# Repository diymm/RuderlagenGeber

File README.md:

## RuderlagenGeber NMEA 2000
Sensor im Eigenbau mit N2K Schnittstelle.

### Mechanischer Aufbau
Durch die Verwendung von Aluminium Blechteilen und Normteilen wird 
ein preisgünstigen Aufbau ermöglicht.\
Die Positionserfassung erfolgt magnetisch verschleissfrei und wird über 360°,\
ohne Anschlag erfasst. Eine mechanische Ausrichtung des Gebers ist nicht notwendig.
Über einen Taster wird die 0° Grad Position festgelegt und\
es kann eine Drehrichtungsumkehr eingeschaltet werden.

### Elektronik
Die Schaltung ist gegen Verpolung und Spannungspitzen geschützt\
und besteht im wesentlichen aus drei Komponenten:\
Dem Positionssensor AS5600\
einem CAN BUS Controller MCP2515\
und dem Kontroller SAMD21G17.\
Die Spannungsregelung wird energiesparend über einen Schaltregler geregelt. 
 
### Firmware
Die Firmware ist aktuell noch in der Testphase und wird noch ergänzt.
Im Testmode werden über die RS232 TTL verschiedene Zustände und Messwerte angezeigt,
auch ohne Ausgabe der Werte ist es mit Hilfe der LED möglich den Abstand des Magnetsensors
ausreichend genau einzustellen. 

### Vorstellung des Projekts auf YouTube
Eine Video Unterstützung auf YouTube steht zur weiteren Unterstützung bereit.

### Dokumentation
Durch die Verendung von KiCad für den Schaltplan und FreeCAD für die Zeichnungen ist eine Anpassung
an eigene Vorstellungen möglich.

### Lizenz
Alle Zeichnungen und der Programmcode können frei, nicht kommerziell, verwendet werden.\
creative commons (CC BY-NC 4.0) https://creativecommons.org/licenses/

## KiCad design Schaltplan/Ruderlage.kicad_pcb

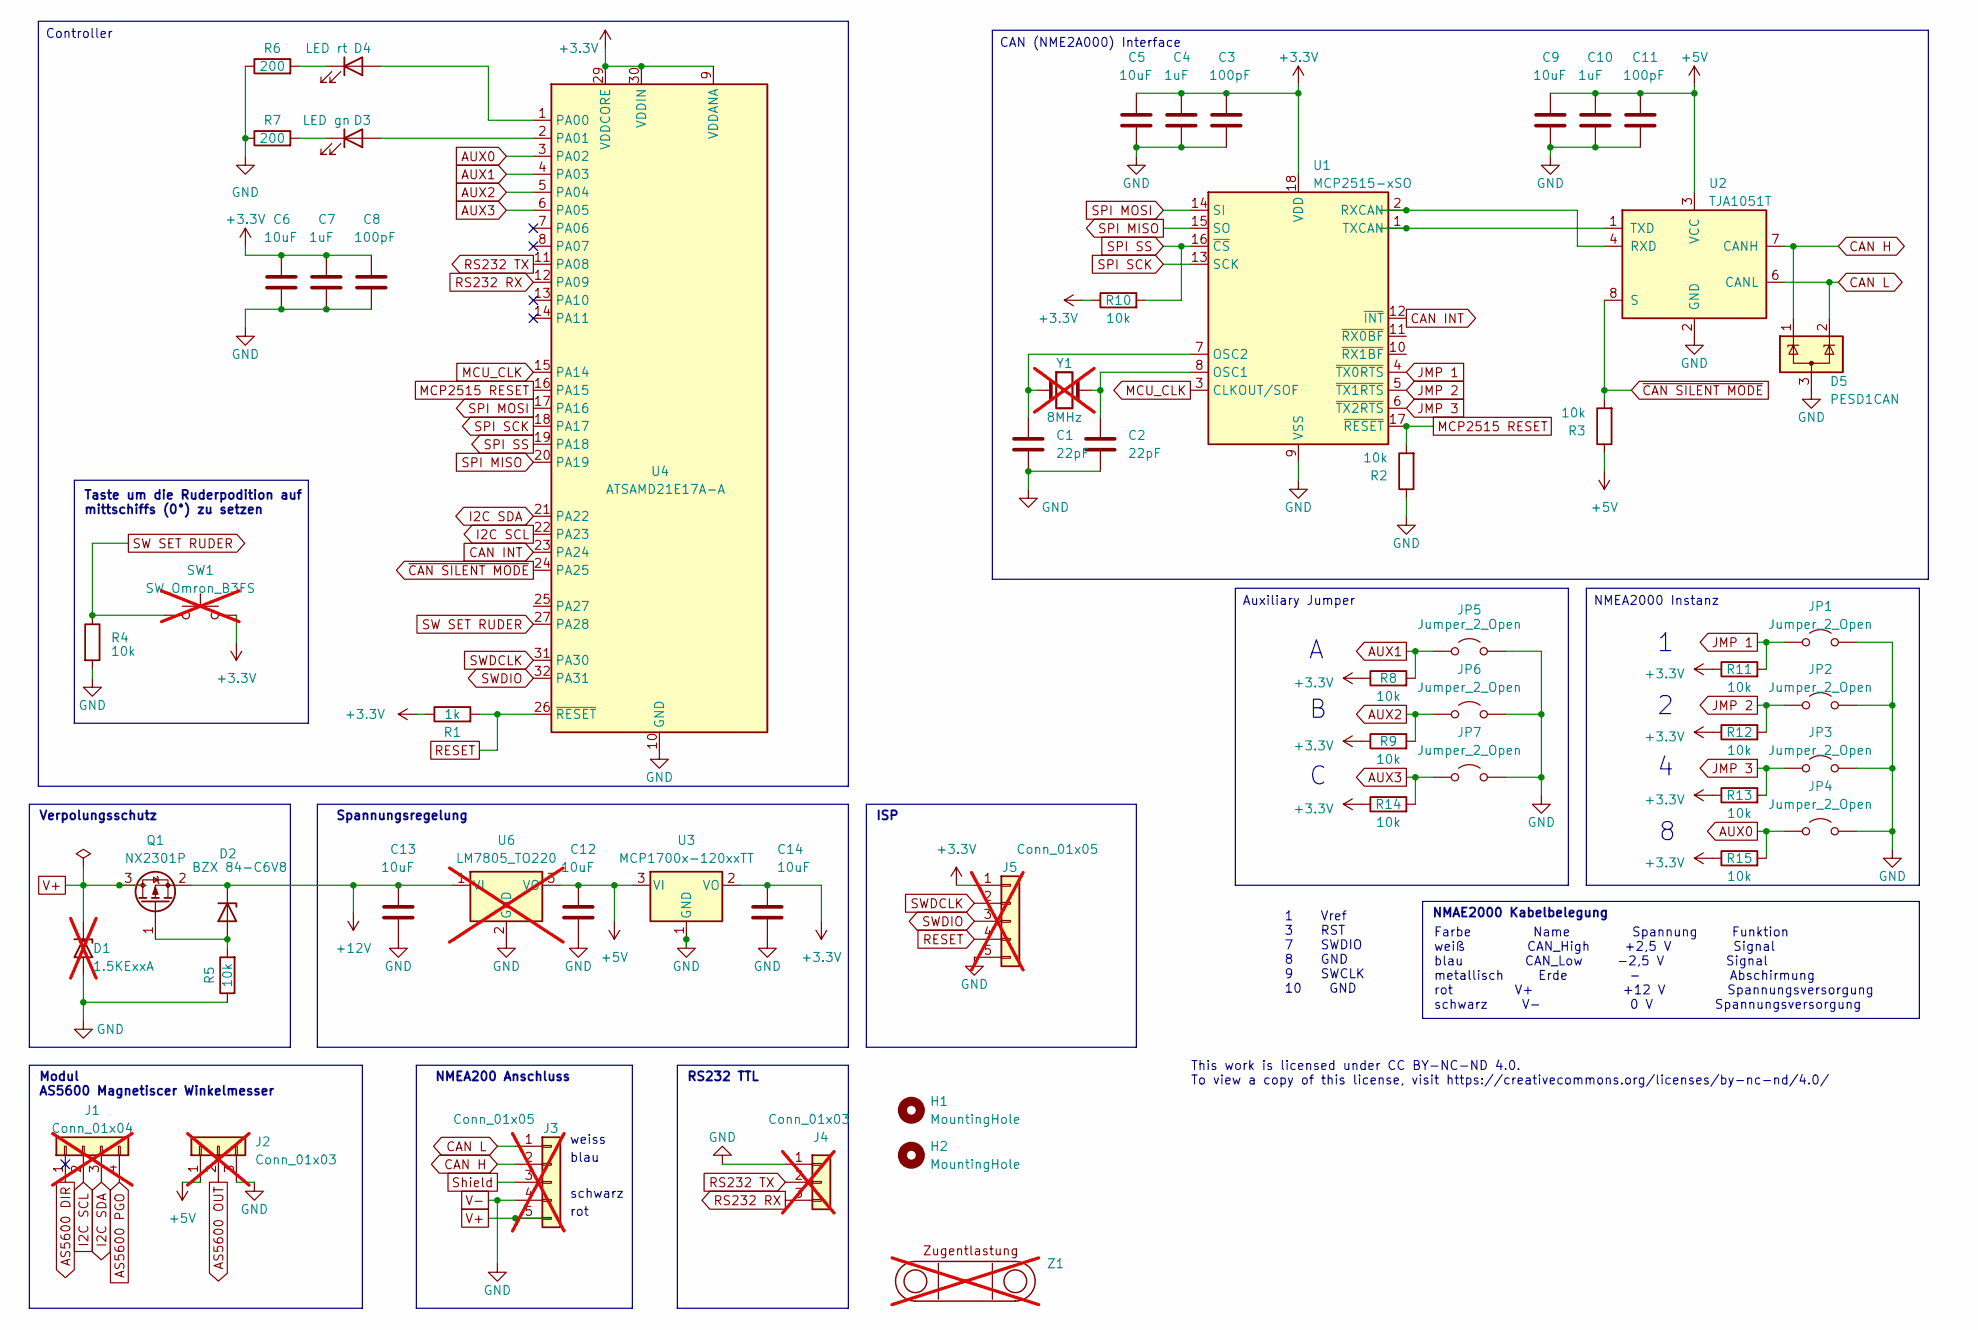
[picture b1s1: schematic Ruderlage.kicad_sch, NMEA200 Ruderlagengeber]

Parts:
C1, C2: 22pF; C_0805_2012Metric
C3, C8, C11: 100pF; C_0805_2012Metric; LCSC C9900195991
C4, C7, C10: 1uF; C_0805_2012Metric
C5, C6, C9, C12, C13, C14: 10uF; C_0805_2012Metric
D1: 1.5KExxA; D_DO-201AE_P15.24mm_Horizontal; not fitted
D2: BZX 84-C6V8; SOT-23
D3: LED gn; LED_0805_2012Metric
D4: LED rt; LED_0805_2012Metric
D5: PESD1CAN; SOT-23
H1, H2: MountingHole; MountingHole_5mm
J1: Conn_01x04; PinHeader_1x04_P2.54mm_Vertical; not fitted
J2, J4: Conn_01x03; PinHeader_1x03_P2.54mm_Vertical; not fitted
J3, J5: Conn_01x05; PinHeader_1x05_P2.54mm_Vertical; not fitted
JP1, JP2, JP3, JP4, JP5, JP6, JP7: Jumper_2_Open; SolderJumper-2_P1.3mm_Open_RoundedPad1.0x1.5mm
Q1: NX2301P; SOT-23; LCSC C551594
R1: 1k; R_0805_2012Metric; LCSC C9900143942
R2, R8, R9, R10, R11, R14, R15: 10k; R_0805_2012Metric; LCSC C9900234692
R3, R4, R5, R12, R13: 10k; R_0805_2012Metric
R6, R7: 200; R_0805_2012Metric; LCSC C2889551
SW1: SW_Omron_B3FS; SW_TH_Tactile_Omron_B3F-10xx; not fitted
U1: MCP2515-xSO; SOIC-18W_7.5x11.6mm_P1.27mm
U2: TJA1051T; SOIC-8_3.9x4.9mm_P1.27mm
U3: MCP1700x-120xxTT; SOT-23
U4: ATSAMD21E17A-A; TQFP-32_7x7mm_P0.8mm; LCSC C618766
U6: LM7805_TO220; TO-220-3_Vertical; not fitted
Y1: 8MHz; Crystal_HC49-4H_Vertical; not fitted
Z1: Zugentlastung; not fitted

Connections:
+3.3V: C3.1, C4.1, C5.1, C6.1, C7.1, C8.1, C14.1, J5.1, R1.1, R8.1, R9.1, R10.1, R11.1, R12.1, R13.1, R14.1, R15.1, SW1.2, U1.18 (VDD), U3.2 (VO), U4.9 (VDDANA), U4.29 (VDDCORE), U4.30 (VDDIN)
+5V: C9.1, C10.1, C11.1, C12.1, J2.1, R3.1, U2.3 (VCC), U3.3 (VI), U6.3 (VO)
+12V: C13.1, D2.3 (K), Q1.2 (S), U6.1 (VI)
AS5600 DIR: J1.1
AS5600 OUT: J2.2
AS5600 PGO: J1.4
AUX0: JP4.1 (A), R15.2, U4.3 (PA02)
AUX1: JP5.1 (A), R8.2, U4.4 (PA03)
AUX2: JP6.1 (A), R9.2, U4.5 (PA04)
AUX3: JP7.1 (A), R14.2, U4.6 (PA05)
CAN H: D5.1 (K), J3.2, U2.7 (CANH)
CAN INT: U1.12 (~INT), U4.23 (PA24)
CAN L: D5.2 (K), J3.1, U2.6 (CANL)
I2C SCL: J1.2, U4.22 (PA23)
I2C SDA: J1.3, U4.21 (PA22)
JMP 1: JP1.1 (A), R11.2, U1.4 (~TX0RTS)
JMP 2: JP2.1 (A), R12.2, U1.5 (~TX1RTS)
JMP 3: JP3.1 (A), R13.2, U1.6 (~TX2RTS)
MCP2515 RESET: R2.2, U1.17 (~RESET), U4.16 (PA15)
MCU_CLK: U1.3 (CLKOUT/SOF), U4.15 (PA14)
unnamed: D2.1 (A), Q1.1 (G), R5.2
unnamed: D3.2 (A), U4.2 (PA01)
unnamed: D3.1 (K), R7.2
unnamed: D4.2 (A), U4.1 (PA00)
unnamed: D4.1 (K), R6.2
unnamed: C2.1, U1.8 (OSC1), Y1.2
unnamed: C1.1, U1.7 (OSC2), Y1.1
unnamed: U1.2 (RXCAN), U2.4 (RXD)
unnamed: U1.1 (TXCAN), U2.1 (TXD)
RESET: J5.4, R1.2, U4.26 (~RESET)
RS232 RX: J4.3, U4.12 (PA09)
RS232 TX: J4.2, U4.11 (PA08)
SPI MISO: U1.15 (SO), U4.20 (PA19)
SPI MOSI: U1.14 (SI), U4.17 (PA16)
SPI SCK: U1.13 (SCK), U4.18 (PA17)
SPI SS: R10.2, U1.16 (~CS), U4.19 (PA18)
SW SET RUDER: R4.1, SW1.1, U4.27 (PA28)
SWDCLK: J5.2, U4.31 (PA30)
SWDIO: J5.3, U4.32 (PA31)
Shield: J3.3
V+: D1.1 (A1), J3.5, Q1.3 (D)
V-: C1.2, C2.2, C3.2, C4.2, C5.2, C6.2, C7.2, C8.2, C9.2, C10.2, C11.2, C12.2, C13.2, C14.2, D1.2 (A2), D5.3 (A), J2.3, J3.4, J4.1, J5.5, JP1.2 (B), JP2.2 (B), JP3.2 (B), JP4.2 (B), JP5.2 (B), JP6.2 (B), JP7.2 (B), R2.1, R4.2, R5.1, R6.1, R7.1, U1.9 (VSS), U2.2 (GND), U3.1 (GND), U4.10 (GND), U4.28 (GND), U6.2 (GND)
~CAN SILENT MODE: R3.2, U2.8 (S), U4.24 (PA25)

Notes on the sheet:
weiss
rot
1 Vref 3 RST 7 SWDIO 8 GND 9 SWCLK 10 GND
Taste um die Ruderpodition auf mittschiffs (0°) zu setzen
Spannungsregelung
This work is licensed under CC BY-NC-ND 4.0. To view a copy of this license, visit https://creativecommons.org/licenses/by-nc-nd/4.0/
ISP
NMAE2000 Kabelbelegung
NMEA200 Anschluss
schwarz
blau
Farbe Name Spannung Funktion weiß CAN_High +2,5 V Signal blau CAN_Low −2,5 V Signal metallisch Erde - Abschirmung rot V+ +12 V Spannungsversorgung schwarz V− 0 V Spannungsversorgung
RS232 TTL
Modul AS5600 Magnetiscer Winkelmesser
Verpolungsschutz
Controller
NMEA2000 Instanz
Auxiliary Jumper
CAN (NME2A000) Interface

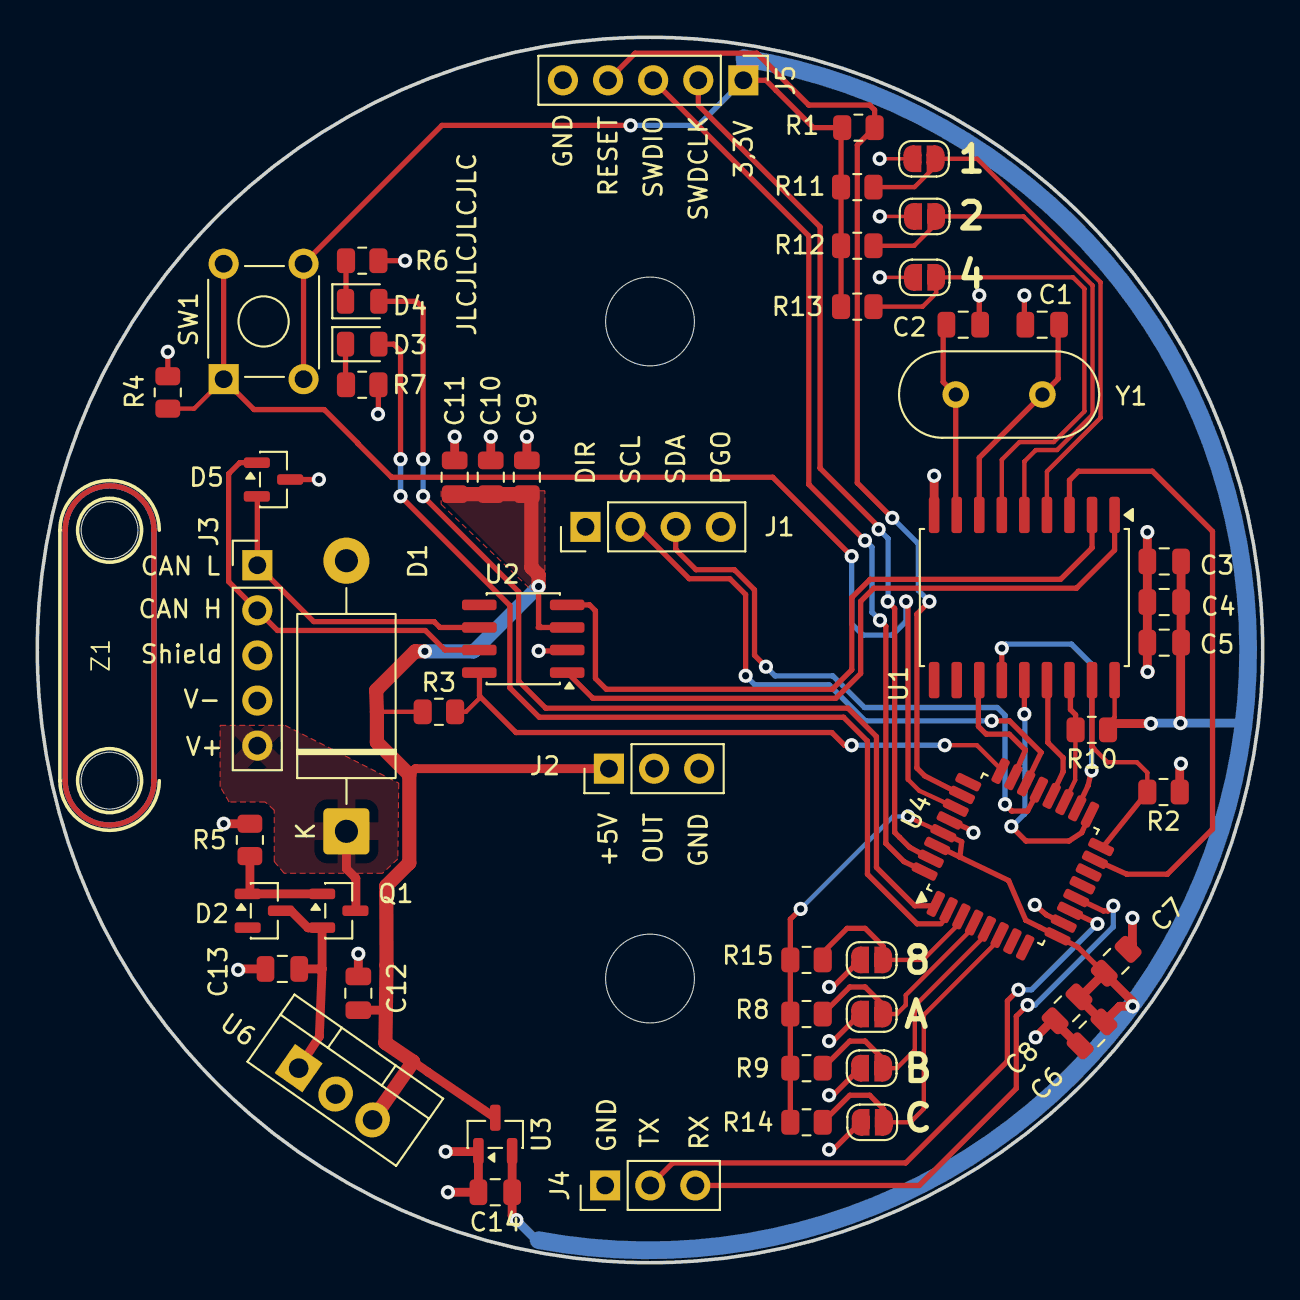
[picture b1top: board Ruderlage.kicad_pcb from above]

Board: 2 copper layers, 69.0 x 69.0 mm, 57 parts (0 on the bottom side), 39 nets.

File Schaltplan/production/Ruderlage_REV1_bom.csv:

Designator,Footprint,Quantity,Value,LCSC Part #
"C1, C2",0805,2,22pF,C123150
"C10, C4, C7",0805,3,1uF,C141772
"C11, C3, C8",0805,3,100pF,C9900195991
"C12, C13, C14, C5, C6, C9",0805,6,10uF,C356840
D1,D_DO-201AE_P15.24mm_Horizontal,1,1.5KExxA,
D2,SOT-23,1,BZX 84-C4V7,C143853
D3,0805,1,LED gn,C2297
D4,0805,1,LED rt,C84256
D5,SOT-23,1,PESD1CAN,
Q1,SOT-23,1,NX2301P,C551594
R1,0805,1,1k,C9900143942
"R10, R11, R14, R15, R2, R8, R9",0805,7,10k,C9900234692
"R12, R13, R3, R4, R5",0805,5,10k,
"R6, R7",0805,2,200,C2889551
SW1,SW_TH_Tactile_Omron_B3F-10xx,1,SW_Omron_B3FS,
U1,SOIC-18W_7.5x11.6mm_P1.27mm,1,MCP2515-xSO,
U2,SOIC-8_3.9x4.9mm_P1.27mm,1,TJA1051T,
U3,SOT-23,1,MCP1700x-120xxTT,
U4,TQFP-32_7x7mm_P0.8mm,1,ATSAMD21E17A-A,C618766
Z1,Zugentlastung,1,~,

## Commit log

2026-01-20 Initial upload
    Projektbeschreibung, Zeichnungen, Schaltplan jedoch noch ohne Firmware.
2026-01-20 Readme ergänzt kleineres ThumbNail
